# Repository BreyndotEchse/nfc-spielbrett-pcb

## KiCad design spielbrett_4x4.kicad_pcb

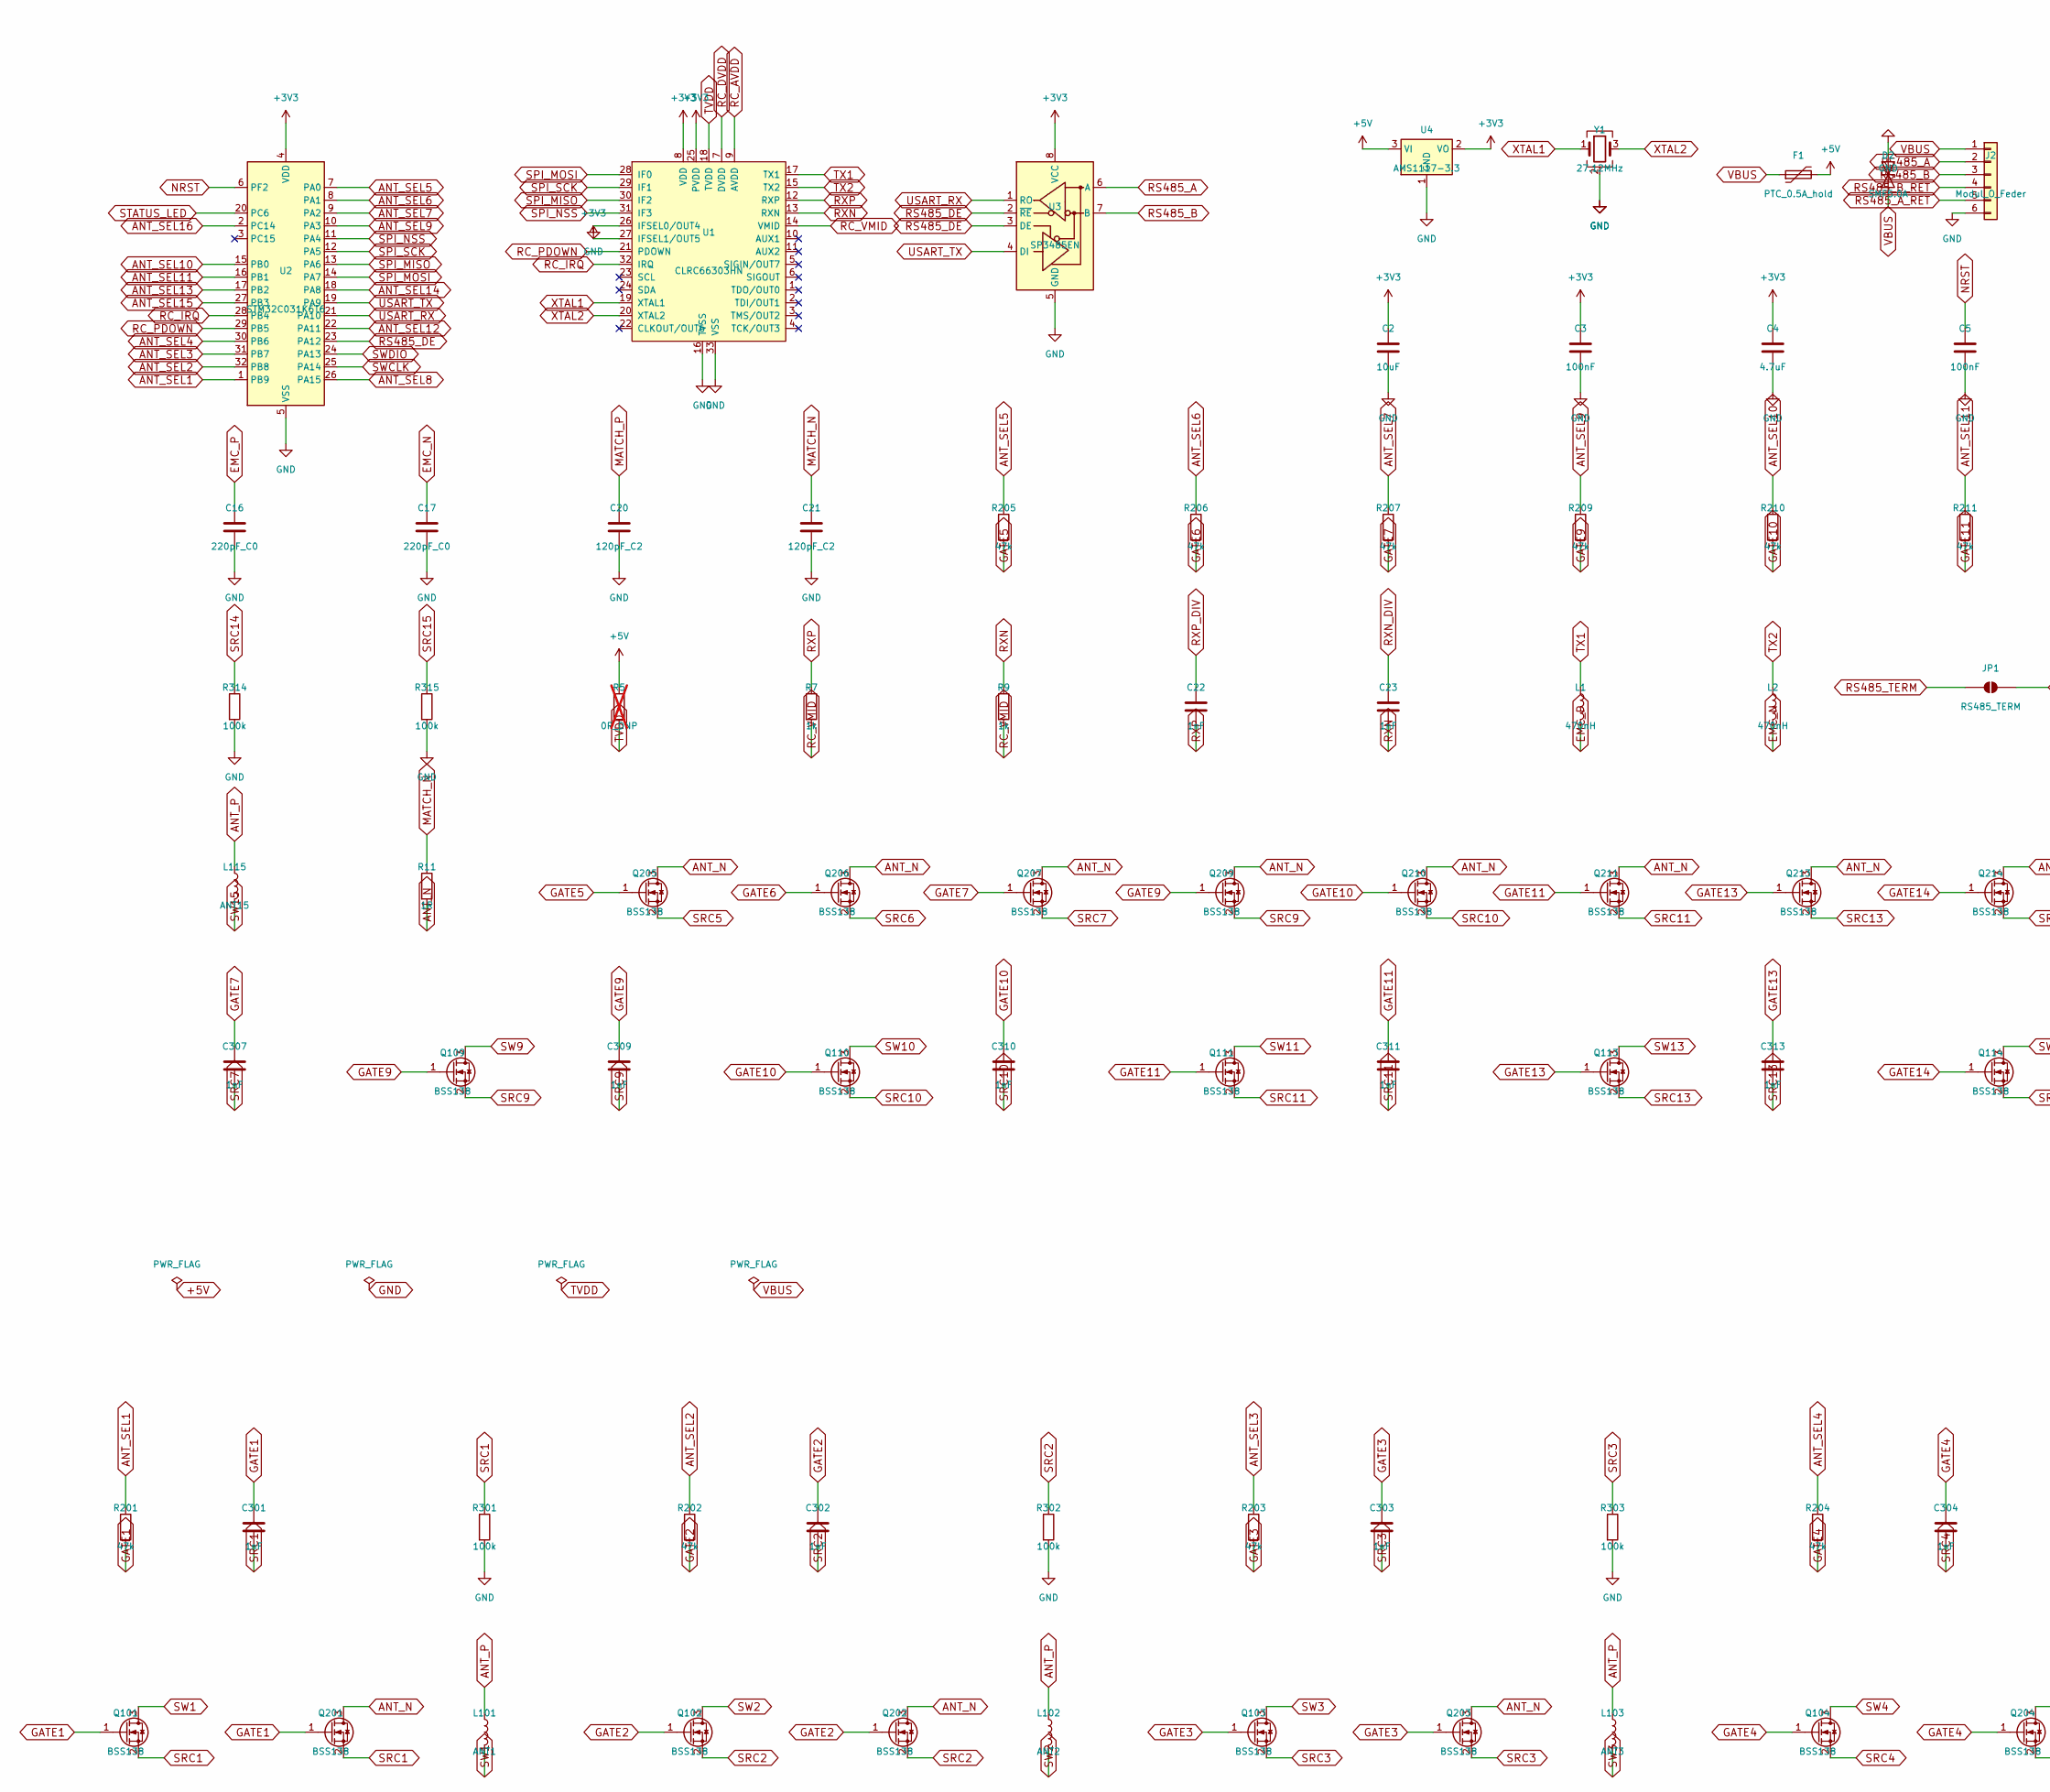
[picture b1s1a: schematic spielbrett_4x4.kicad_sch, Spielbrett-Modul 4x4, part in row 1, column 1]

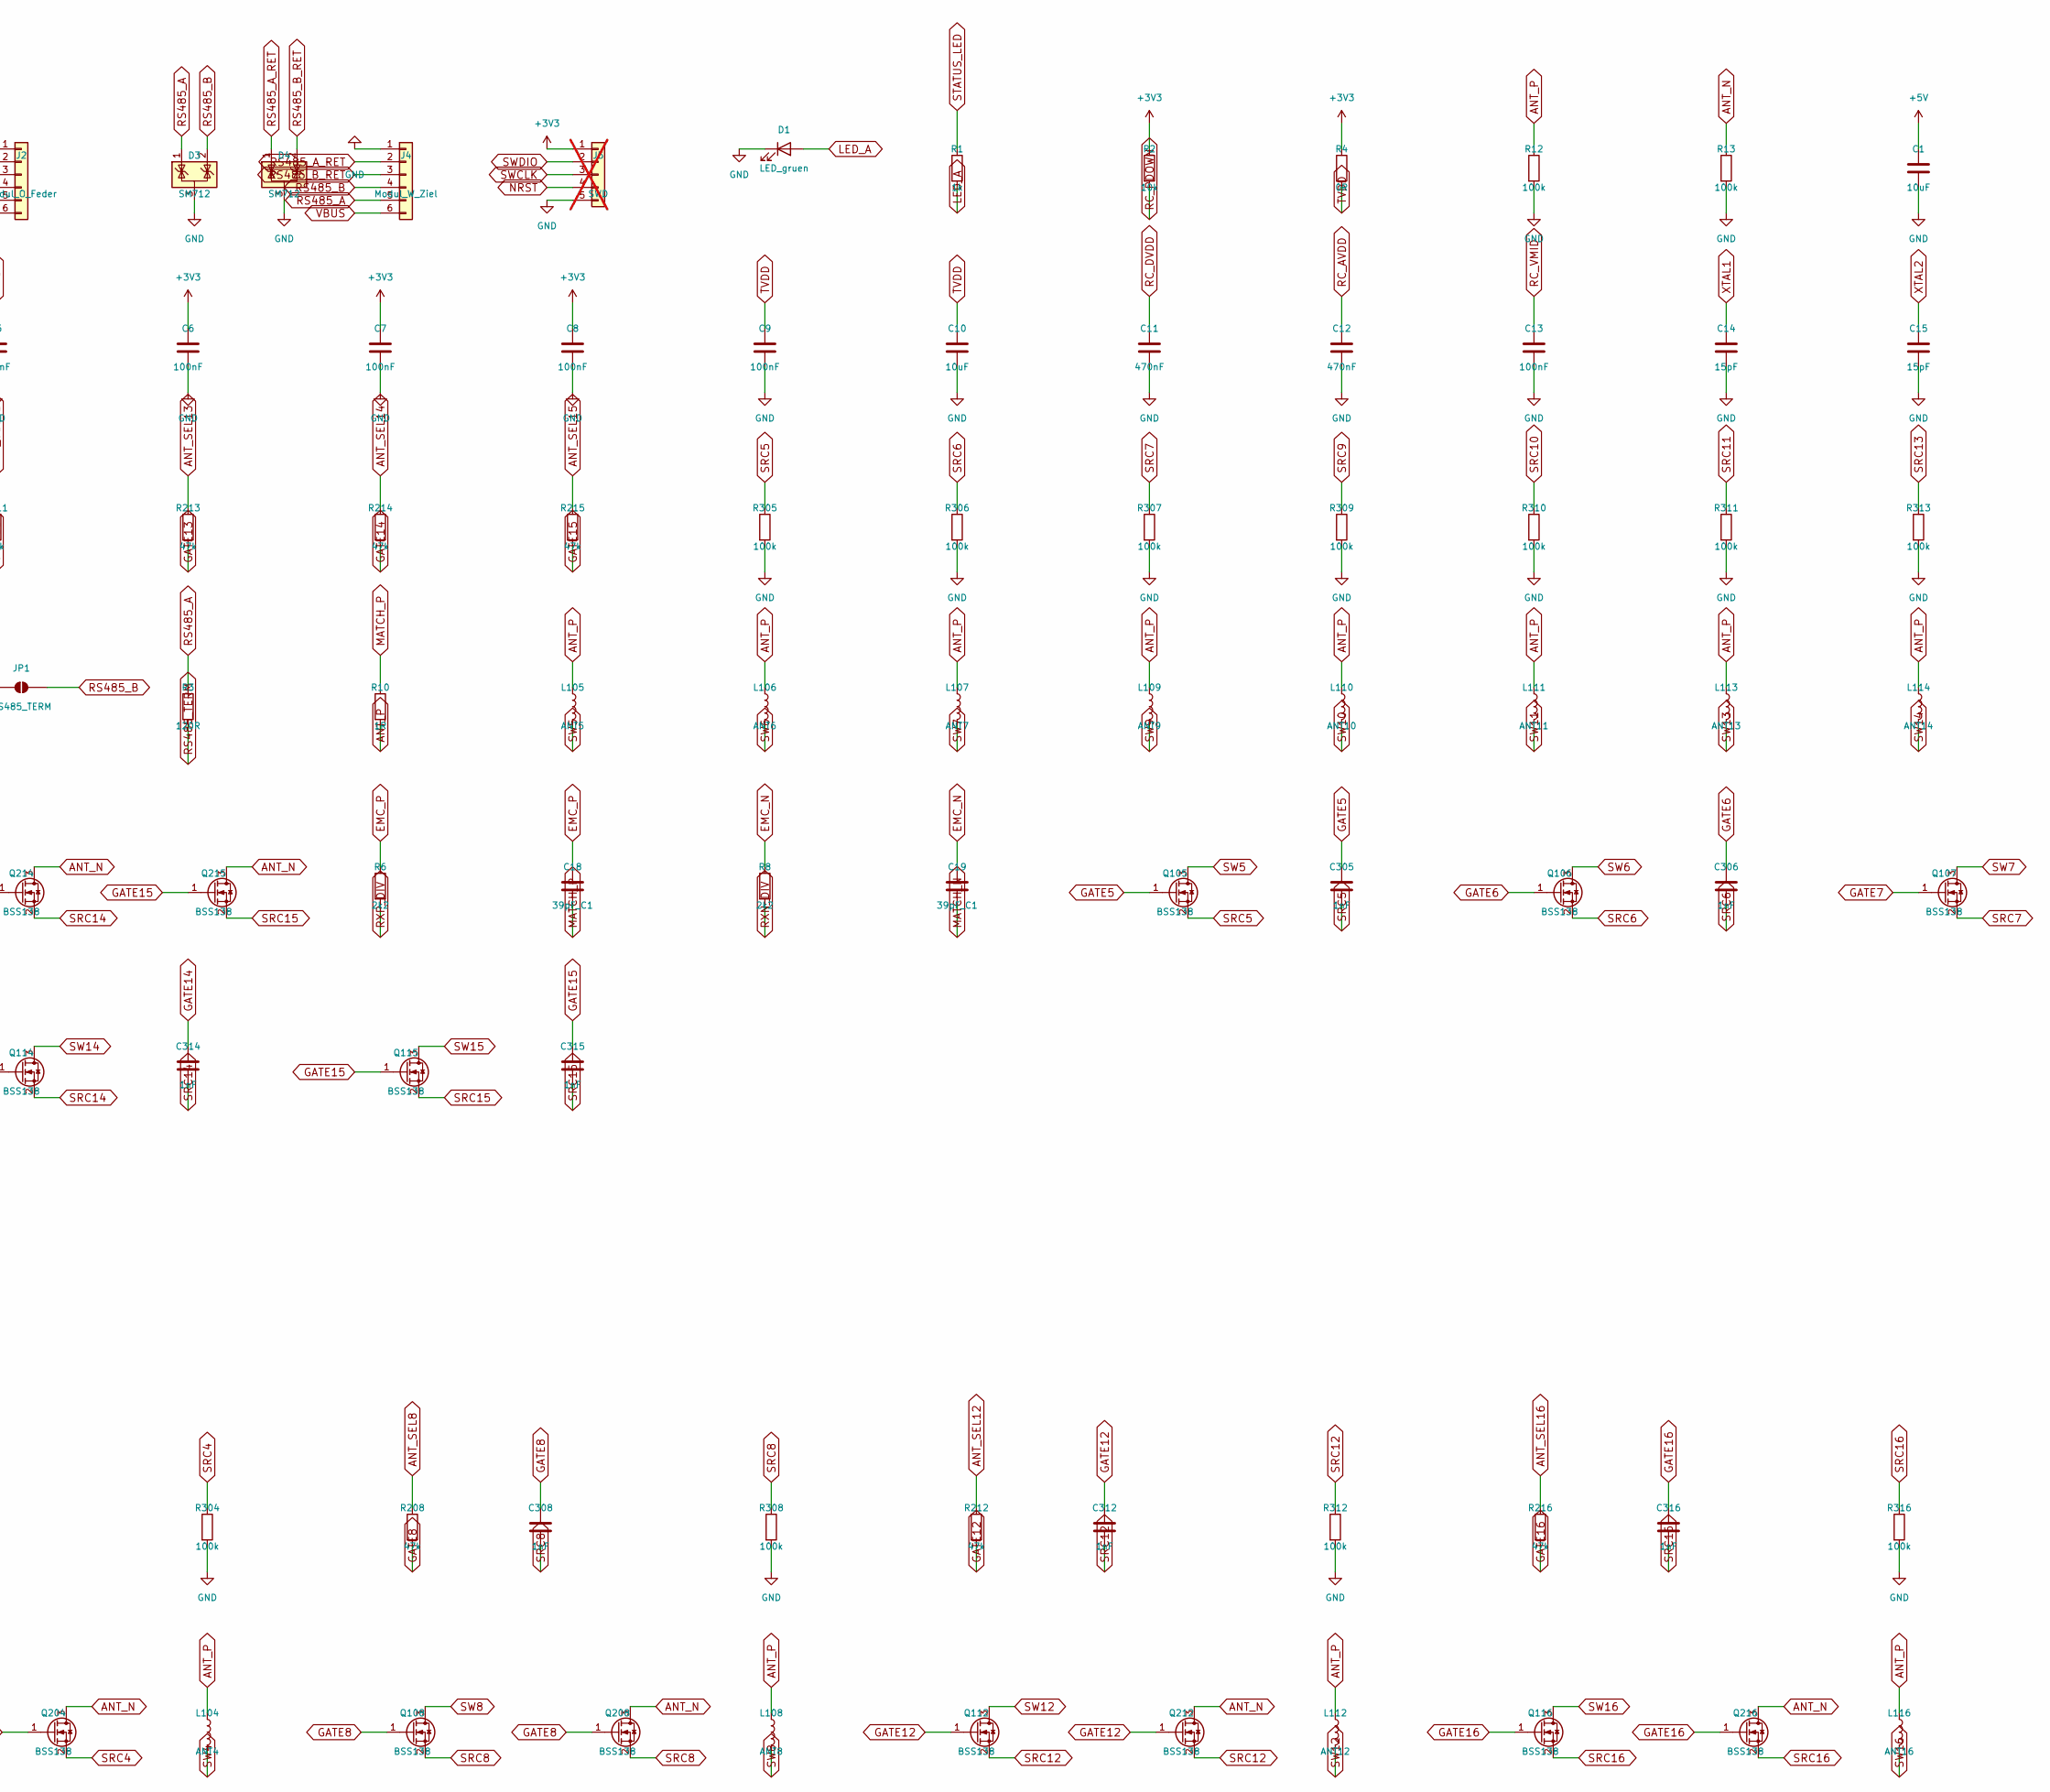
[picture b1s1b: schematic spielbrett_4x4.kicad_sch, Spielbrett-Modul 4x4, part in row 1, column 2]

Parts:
C1, C2, C10: 10uF; C_0805_2012Metric; LCSC C15850
C3, C5, C6, C7, C8, C9, C13: 100nF; C_0603_1608Metric; LCSC C14663
C4: 4.7uF; C_0603_1608Metric; LCSC C19666
C11, C12: 470nF; C_0603_1608Metric; LCSC C1623
C14, C15: 15pF; C_0603_1608Metric; LCSC C1644
C16, C17: 220pF_C0; C_0603_1608Metric; LCSC C106210
C18, C19: 39pF_C1; C_0603_1608Metric; LCSC C107049
C20, C21: 120pF_C2; C_0603_1608Metric; LCSC C107035
C22, C23, C301, C302, C303, C304, C305, C306, C307, C308, C309, C310, C311, C312, C313, C314, C315, C316: 1nF; C_0603_1608Metric; LCSC C1588
D1: LED_gruen; LED_0603_1608Metric; LCSC C12624
D2: SMF5.0A; D_SOD-123F; LCSC C19077497
D3, D4: SM712; SOT-23; LCSC C521963
F1: PTC_0.5A_hold; Fuse_1206_3216Metric; LCSC C7542947
J2: Modul_O_Feder; HC-CX-PH254-1x6PW-4050B-E; MPN HC-CX-PH254-1x6PW-4050B-E; LCSC C56314391
J4: Modul_W_Ziel; HC-CX-FH254-1x6PW-4040B-E; MPN HC-CX-FH254-1x6PW-4040B-E; LCSC C56314419
J5: SWD; PinHeader_1x05_P1.27mm_Vertical; not fitted
JP1: RS485_TERM; SolderJumper-2_P1.3mm_Open_RoundedPad1.0x1.5mm
L1, L2: 470nH; L_0805_2012Metric; LCSC C412002
L101: ANT1; NFC_Coil_D30_N4_W0.4_S0.4
L102: ANT2; NFC_Coil_D30_N4_W0.4_S0.4
L103: ANT3; NFC_Coil_D30_N4_W0.4_S0.4
L104: ANT4; NFC_Coil_D30_N4_W0.4_S0.4
L105: ANT5; NFC_Coil_D30_N4_W0.4_S0.4
L106: ANT6; NFC_Coil_D30_N4_W0.4_S0.4
L107: ANT7; NFC_Coil_D30_N4_W0.4_S0.4
L108: ANT8; NFC_Coil_D30_N4_W0.4_S0.4
L109: ANT9; NFC_Coil_D30_N4_W0.4_S0.4
L110: ANT10; NFC_Coil_D30_N4_W0.4_S0.4
L111: ANT11; NFC_Coil_D30_N4_W0.4_S0.4
L112: ANT12; NFC_Coil_D30_N4_W0.4_S0.4
L113: ANT13; NFC_Coil_D30_N4_W0.4_S0.4
L114: ANT14; NFC_Coil_D30_N4_W0.4_S0.4
L115: ANT15; NFC_Coil_D30_N4_W0.4_S0.4
L116: ANT16; NFC_Coil_D30_N4_W0.4_S0.4
Q101, Q102, Q103, Q104, Q105, Q106, Q107, Q108, Q109, Q110, Q111, Q112, Q113, Q114, Q115, Q116, Q201, Q202, Q203, Q204, Q205, Q206, Q207, Q208, Q209, Q210, Q211, Q212, Q213, Q214, Q215, Q216: BSS138; SOT-23; LCSC C7420339
R1, R7, R9: 1k; R_0603_1608Metric; LCSC C21190
R2: 10k; R_0603_1608Metric; LCSC C25804
R3: 120R; R_0603_1608Metric; LCSC C22787
R4: 0R; R_0805_2012Metric; LCSC C17477
R5: 0R_DNP; R_0805_2012Metric; LCSC C17477; not fitted
R6, R8: 2k2; R_0603_1608Metric; LCSC C4190
R10, R11: 1R; R_0603_1608Metric; LCSC C22936
R12, R13, R301, R302, R303, R304, R305, R306, R307, R308, R309, R310, R311, R312, R313, R314, R315, R316: 100k; R_0603_1608Metric; LCSC C25803
R201, R202, R203, R204, R205, R206, R207, R208, R209, R210, R211, R212, R213, R214, R215, R216: 47k; R_0603_1608Metric; LCSC C25819
U1: CLRC66303HN; HVQFN-32-1EP_5x5mm_P0.5mm_EP3.1x3.1mm; MPN CLRC66303HNY; LCSC C2988350
U2: STM32C031K6T6; LQFP-32_7x7mm_P0.8mm; MPN STM32C031K6T6; LCSC C5456169
U3: SP3485EN; SOIC-8_3.9x4.9mm_P1.27mm; MPN SP3485EN-L/TR; LCSC C8963
U4: AMS1117-3.3; SOT-223-3_TabPin2; LCSC C6186
Y1: 27.12MHz; Crystal_SMD_3225-4Pin_3.2x2.5mm; LCSC C29975

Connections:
+3V3: C2.1, C3.1, C4.1, C6.1, C7.1, C8.1, J5.1, R2.1, R4.1, U1.8 (VDD), U1.25 (PVDD), U1.27 (IFSEL1/OUT5), U2.4 (VDD), U3.8 (VCC), U4.2 (VO)
+5V: C1.1, F1.2, R5.1, U4.3 (VI)
ANT_N: Q201.3 (D), Q202.3 (D), Q203.3 (D), Q204.3 (D), Q205.3 (D), Q206.3 (D), Q207.3 (D), Q208.3 (D), Q209.3 (D), Q210.3 (D), Q211.3 (D), Q212.3 (D), Q213.3 (D), Q214.3 (D), Q215.3 (D), Q216.3 (D), R11.2, R13.1
ANT_P: L101.1, L102.1, L103.1, L104.1, L105.1, L106.1, L107.1, L108.1, L109.1, L110.1, L111.1, L112.1, L113.1, L114.1, L115.1, L116.1, R10.2, R12.1
ANT_SEL1: R201.1, U2.1 (PB9)
ANT_SEL2: R202.1, U2.32 (PB8)
ANT_SEL3: R203.1, U2.31 (PB7)
ANT_SEL4: R204.1, U2.30 (PB6)
ANT_SEL5: R205.1, U2.7 (PA0)
ANT_SEL6: R206.1, U2.8 (PA1)
ANT_SEL7: R207.1, U2.9 (PA2)
ANT_SEL8: R208.1, U2.26 (PA15)
ANT_SEL9: R209.1, U2.10 (PA3)
ANT_SEL10: R210.1, U2.15 (PB0)
ANT_SEL11: R211.1, U2.16 (PB1)
ANT_SEL12: R212.1, U2.22 (PA11)
ANT_SEL13: R213.1, U2.17 (PB2)
ANT_SEL14: R214.1, U2.18 (PA8)
ANT_SEL15: R215.1, U2.27 (PB3)
ANT_SEL16: R216.1, U2.2 (PC14)
EMC_N: C17.1, C19.1, L2.2, R8.1
EMC_P: C16.1, C18.1, L1.2, R6.1
GATE1: C301.1, Q101.1 (G), Q201.1 (G), R201.2
GATE2: C302.1, Q102.1 (G), Q202.1 (G), R202.2
GATE3: C303.1, Q103.1 (G), Q203.1 (G), R203.2
GATE4: C304.1, Q104.1 (G), Q204.1 (G), R204.2
GATE5: C305.1, Q105.1 (G), Q205.1 (G), R205.2
GATE6: C306.1, Q106.1 (G), Q206.1 (G), R206.2
GATE7: C307.1, Q107.1 (G), Q207.1 (G), R207.2
GATE8: C308.1, Q108.1 (G), Q208.1 (G), R208.2
GATE9: C309.1, Q109.1 (G), Q209.1 (G), R209.2
GATE10: C310.1, Q110.1 (G), Q210.1 (G), R210.2
GATE11: C311.1, Q111.1 (G), Q211.1 (G), R211.2
GATE12: C312.1, Q112.1 (G), Q212.1 (G), R212.2
GATE13: C313.1, Q113.1 (G), Q213.1 (G), R213.2
GATE14: C314.1, Q114.1 (G), Q214.1 (G), R214.2
GATE15: C315.1, Q115.1 (G), Q215.1 (G), R215.2
GATE16: C316.1, Q116.1 (G), Q216.1 (G), R216.2
GND: C1.2, C2.2, C3.2, C4.2, C5.2, C6.2, C7.2, C8.2, C9.2, C10.2, C11.2, C12.2, C13.2, C14.2, C15.2, C16.2, C17.2, C20.2, C21.2, D1.1 (K), D2.2 (A2), D3.3 (A), D4.3 (A), J2.6, J4.1, J5.5, R12.2, R13.2, R301.2, R302.2, R303.2, R304.2, R305.2, R306.2, R307.2, R308.2, R309.2, R310.2, R311.2, R312.2, R313.2, R314.2, R315.2, R316.2, U1.16 (TVSS), U1.26 (IFSEL0/OUT4), U1.33 (VSS), U2.5 (VSS), U3.5 (GND), U4.1 (GND), Y1.2 (G), Y1.4 (G)
LED_A: D1.2 (A), R1.2
MATCH_N: C19.2, C21.1, R11.1
MATCH_P: C18.2, C20.1, R10.1
NRST: C5.1, J5.4, U2.6 (PF2)
RC_AVDD: C12.1, U1.9 (AVDD)
RC_DVDD: C11.1, U1.7 (DVDD)
RC_IRQ: U1.32 (IRQ), U2.28 (PB4)
RC_PDOWN: R2.2, U1.21 (PDOWN), U2.29 (PB5)
RC_VMID: C13.1, R7.2, R9.2, U1.14 (VMID)
RS485_A: D3.1 (K), J2.2, J4.5, R3.1, U3.6 (A)
RS485_A_RET: D4.1 (K), J2.5, J4.2
RS485_B: D3.2 (K), J2.3, J4.4, JP1.2 (B), U3.7 (B)
RS485_B_RET: D4.2 (K), J2.4, J4.3
RS485_DE: U2.23 (PA12), U3.2 (~RE), U3.3 (DE)
RS485_TERM: JP1.1 (A), R3.2
RXN: C23.2, R9.1, U1.13 (RXN)
RXN_DIV: C23.1, R8.2
RXP: C22.2, R7.1, U1.12 (RXP)
RXP_DIV: C22.1, R6.2
SPI_MISO: U1.30 (IF2), U2.13 (PA6)
SPI_MOSI: U1.28 (IF0), U2.14 (PA7)
SPI_NSS: U1.31 (IF3), U2.11 (PA4)
SPI_SCK: U1.29 (IF1), U2.12 (PA5)
SRC1: C301.2, Q101.2 (S), Q201.2 (S), R301.1
SRC2: C302.2, Q102.2 (S), Q202.2 (S), R302.1
SRC3: C303.2, Q103.2 (S), Q203.2 (S), R303.1
SRC4: C304.2, Q104.2 (S), Q204.2 (S), R304.1
SRC5: C305.2, Q105.2 (S), Q205.2 (S), R305.1
SRC6: C306.2, Q106.2 (S), Q206.2 (S), R306.1
SRC7: C307.2, Q107.2 (S), Q207.2 (S), R307.1
SRC8: C308.2, Q108.2 (S), Q208.2 (S), R308.1
SRC9: C309.2, Q109.2 (S), Q209.2 (S), R309.1
SRC10: C310.2, Q110.2 (S), Q210.2 (S), R310.1
SRC11: C311.2, Q111.2 (S), Q211.2 (S), R311.1
SRC12: C312.2, Q112.2 (S), Q212.2 (S), R312.1
SRC13: C313.2, Q113.2 (S), Q213.2 (S), R313.1
SRC14: C314.2, Q114.2 (S), Q214.2 (S), R314.1
SRC15: C315.2, Q115.2 (S), Q215.2 (S), R315.1
SRC16: C316.2, Q116.2 (S), Q216.2 (S), R316.1
STATUS_LED: R1.1, U2.20 (PC6)
SW1: L101.2, Q101.3 (D)
SW2: L102.2, Q102.3 (D)
SW3: L103.2, Q103.3 (D)
SW4: L104.2, Q104.3 (D)
SW5: L105.2, Q105.3 (D)
SW6: L106.2, Q106.3 (D)
SW7: L107.2, Q107.3 (D)
SW8: L108.2, Q108.3 (D)
SW9: L109.2, Q109.3 (D)
SW10: L110.2, Q110.3 (D)
SW11: L111.2, Q111.3 (D)
SW12: L112.2, Q112.3 (D)
SW13: L113.2, Q113.3 (D)
SW14: L114.2, Q114.3 (D)
SW15: L115.2, Q115.3 (D)
SW16: L116.2, Q116.3 (D)
SWCLK: J5.3, U2.25 (PA14)
SWDIO: J5.2, U2.24 (PA13)
TX1: L1.1, U1.17 (TX1)
TX2: L2.1, U1.15 (TX2)
USART_RX: U2.21 (PA10), U3.1 (RO)
USART_TX: U2.19 (PA9), U3.4 (DI)
XTAL1: C14.1, U1.19 (XTAL1), Y1.1
XTAL2: C15.1, U1.20 (XTAL2), Y1.3

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
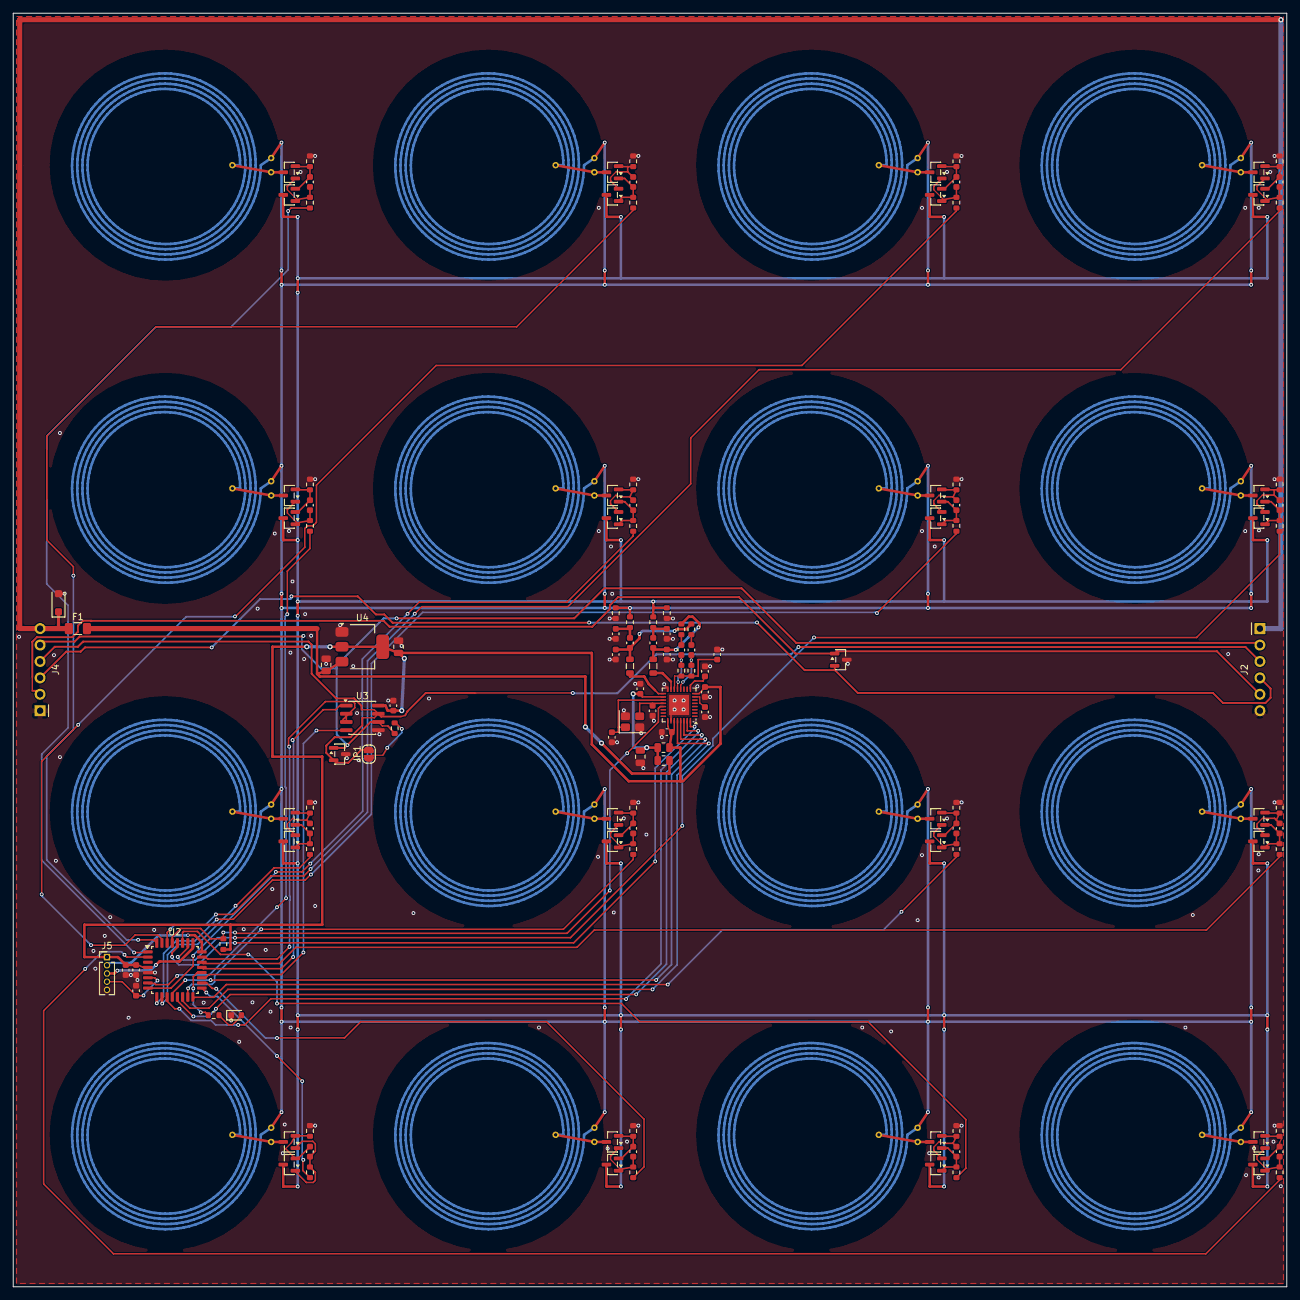
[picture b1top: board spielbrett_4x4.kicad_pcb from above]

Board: 2 copper layers, 197.0 x 197.0 mm, 148 parts (0 on the bottom side), 105 nets.

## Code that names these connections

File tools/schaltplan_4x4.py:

"""Schaltplan des 4x4-Moduls (spielbrett_4x4.kicad_sch) aus dem 3x3-Schaltplan erzeugen.

  python tools/schaltplan_4x4.py

Das 4x4-Brett entsteht aus dem 3x3-Brett, indem rechts eine Spalte und oben eine Reihe Felder
angesetzt werden. Die Spulen werden im 4x4-Raster zeilenweise neu nummeriert (ANT1 oben links,
ANT16 unten rechts); die bisherigen 9 Spulen liegen in den Reihen 2-4 / Spalten 1-3.

  * Referenzen je Spule k (1..16): L1kk Spule, Q1kk Schalter Spulenseite, Q2kk Schalter ANT_N,
    R2kk Gate-Widerstand, R3kk Source-Bezug, C3kk Gate-Kondensator (z. B. L101, Q216)
  * Netze je Spule: ANT_SELk, GATEk, SRCk, SWk; Spulenwert ANTk
  * Die 7 neuen Spulengruppen sind Kopien der bisherigen Gruppe 9 (unten auf dem Blatt)
  * Neue Auswahlleitungen an bisher freien MCU-Pins (PC15 bleibt frei):
      ANT_SEL1 PB9, ANT_SEL2 PB8, ANT_SEL3 PB7, ANT_SEL4 PB6 (obere Reihe),
      ANT_SEL8 PA15, ANT_SEL12 PA11, ANT_SEL16 PC14 (rechte Spalte)
"""
import re
import uuid
from pathlib import Path

PRJ = Path(__file__).resolve().parent.parent
SRC = PRJ / "spielbrett.kicad_sch"
DST = PRJ / "spielbrett_4x4.kicad_sch"

OLD_N, NEW_N = 3, 4


def new_k(k_old):
    r, c = divmod(k_old - 1, OLD_N)
    return (r + 1) * NEW_N + c + 1


MAP = {k: new_k(k) for k in range(1, OLD_N * OLD_N + 1)}           # 1->5 ... 9->15
NEW_COILS = sorted(set(range(1, NEW_N * NEW_N + 1)) - set(MAP.values()))
# MCU-Pin (Pin-Endpunkt im Schaltplan) je neuer Auswahlleitung; Seite L = links (Label nach links)
GPIO = {1: ("L", 102.87), 2: ("L", 100.33), 3: ("L", 97.79), 4: ("L", 95.25),
        8: ("R", 102.87), 12: ("R", 92.71), 16: ("L", 72.39)}
PIN_X = {"L": 62.23, "R": 82.55}


def refs(k):
    return {"L": f"L{100 + k}", "Q": f"Q{100 + k}", "QN": f"Q{200 + k}",
            "RG": f"R{200 + k}", "RS": f"R{300 + k}", "C": f"C{300 + k}"}


def old_refs(k):
    return {"L": f"L1{k}", "Q": f"Q{k}", "QN": f"Q1{k}", "RG": f"R2{k}", "RS": f"R3{k}", "C": f"C3{k}"}


def blocks(s):
    """Top-Level-Elemente (Einrueckung ein Tab) als (start, ende)."""
    out = []
    for m in re.finditer(r"^\t\(", s, re.M):
        a = m.start()
        b = s.find("\n\t)\n", a)
        nl = s.find("\n", a)
        if s[a:nl].rstrip().endswith(")"):        # einzeiliges Element
            b = nl
        else:
            b += 3
        out.append((a, b))
    return out


def pts(blk):
    p = re.findall(r"\(xy ([\d.\-]+) ([\d.\-]+)\)", blk) if blk.startswith("\t(wire") else []
    if not p:
        m = re.search(r"\(at ([\d.\-]+) ([\d.\-]+)", blk)
        p = [m.groups()] if m else []
    return [(float(x), float(y)) for x, y in p]


def fmt(v):
    r = round(v, 4)
    return str(int(r)) if r == int(r) else repr(r)


def shift(blk, dx, dy):
    def f(m):
        return f"({m.group(1)} {fmt(float(m.group(2)) + dx)} {fmt(float(m.group(3)) + dy)}"
    return re.sub(r"\((at|xy) ([\d.\-]+) ([\d.\-]+)", f, blk)


def fresh_uuids(blk):
    return re.sub(r'\(uuid "[0-9a-f-]{36}"\)', lambda m: f'(uuid "{uuid.uuid4()}")', blk)


def main():
    s = SRC.read_text(encoding="utf-8").replace("\r\n", "\n")

    # 1) bestehende 9 Spulengruppen umbenennen (gleichzeitig, ohne Verkettung)
    ref_map = {}
    for k_old, k in MAP.items():
        for key, old in old_refs(k_old).items():
            ref_map[old] = refs(k)[key]
    s = re.sub(r'(\(property "Reference" |\(reference )"([^"]+)"',
               lambda m: f'{m.group(1)}"{ref_map.get(m.group(2), m.group(2))}"', s)
    s = re.sub(r'\(global_label "(ANT_SEL|GATE|SRC|SW)(\d+)"',
               lambda m: f'(global_label "{m.group(1)}{MAP[int(m.group(2))]}"', s)
    s = re.sub(r'\(property "Value" "ANT(\d)"', lambda m: f'(property "Value" "ANT{MAP[int(m.group(1))]}"', s)
    s = s.replace('(project "spielbrett"', '(project "spielbrett_4x4"')
    s = re.sub(r'\(title "[^"]*"\)', '(title "Spielbrett-Modul 4x4")', s, count=1)

    # 2) Vorlage: Gruppe der bisherigen Spule 9 (jetzt 15) -- je Bauteil Symbol + Draehte + Labels
    bl = blocks(s)
    tpl_k = MAP[9]
    tpl = {}
    for key, ref in refs(tpl_k).items():
        sym = next((a, b) for a, b in bl if s[a:b].startswith("\t(symbol")
                   and f'(property "Reference" "{ref}"' in s[a:b])
        c = pts(s[sym[0]:sym[1]])[0]
        members = [s[a:b] for a, b in bl
                   if not s[a:b].startswith("\t(lib_symbols")
                   and any(abs(x - c[0]) < 13 and abs(y - c[1]) < 13 for x, y in pts(s[a:b]))]
        tpl[key] = (c, members)

    pwr = max(int(n) for n in re.findall(r'"#PWR(\d+)"', s))
    G = 1.27
    slots = {"RG": (0, 260), "C": (20, 260), "RS": (56, 260), "Q": (0, 292), "QN": (32, 292), "L": (56, 292)}
    add = []
    for j, k in enumerate(NEW_COILS):
        bx = 32 + 88 * j                                          # Rastereinheiten (1,27 mm)
        for key, (c, members) in tpl.items():
            sx, sy = slots[key]
            dx, dy = (bx + sx) * G - c[0], sy * G - c[1]
            for blk in members:
                b = shift(fresh_uuids(blk), dx, dy)
                for kk, ref in refs(tpl_k).items():
                    b = b.replace(f'"{ref}"', f'"{refs(k)[kk]}"')
                b = re.sub(r'"(ANT_SEL|GATE|SRC|SW)%d"' % tpl_k, lambda m: f'"{m.group(1)}{k}"', b)
                b = b.replace(f'"ANT{tpl_k}"', f'"ANT{k}"')
                if '"#PWR' in b:
                    pwr += 1
                    b = re.sub(r'"#PWR\d+"', f'"#PWR{pwr:03d}"', b)
                add.append(b)

    # 3) MCU: freie Pins (No-Connect) durch Draht + Label ANT_SELk ersetzen
    lab = {}
    for side, name in (("L", "ANT_SEL15"), ("R", "ANT_SEL14")):   # vorhandene Labels als Vorlage
        m = re.search(r'\t\(global_label "%s"\n\t\t\(shape bidirectional\)\n\t\t\(at (%s) ([\d.]+)' %
                      (name, "55.88" if side == "L" else "88.9"), s)
        a = m.start()
        lab[side] = (s[a:s.find("\n\t)\n", a) + 3], float(m.group(2)))
    for k, (side, y) in GPIO.items():
        px = PIN_X[side]
        nc = re.search(r'\t\(no_connect\n\t\t\(at %s %s\)\n.*?\n\t\)\n' % (re.escape(f"{px:g}"), re.escape(f"{y:g}")), s)
        if not nc:
            raise SystemExit(f"Kein No-Connect an MCU-Pin {side} y={y}")
        s = s[:nc.start()] + s[nc.end():]
        lx = px - 6.35 if side == "L" else px + 6.35
        add.append(f'\t(wire\n\t\t(pts (xy {px:g} {y:g}) (xy {lx:g} {y:g}))\n'
                   f'\t\t(stroke (width 0) (type solid))\n\t\t(uuid "{uuid.uuid4()}")\n\t)\n')
        blk, y0 = lab[side]
        b = shift(fresh_uuids(blk), 0, y - y0)
        b = re.sub(r'\(global_label "ANT_SEL\d+"', f'(global_label "ANT_SEL{k}"', b)
        add.append(b)

    i = s.index("\t(sheet_instances")
    s = s[:i] + "".join(a if a.endswith("\n") else a + "\n" for a in add) + s[i:]
    DST.write_bytes(s.replace("\n", "\r\n").encode("utf-8"))
    print(f"{DST.name}: {len(NEW_COILS)} neue Spulengruppen ({NEW_COILS}), Umbenennung {MAP}")


if __name__ == "__main__":
    main()

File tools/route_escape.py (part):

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
Alles landet gesperrt in der Gruppe "Escape_Routing"; ein erneuter Lauf ersetzt nur diese Gruppe.

RX     RXN (Pin 13) / RXP (Pin 12) per Via unter den VMID-Pads von R9/R7 hindurch auf B.Cu zum
       Knoten R.1/C.2 (eine Kreuzung VMID <-> RX ist bei dieser Pinfolge topologisch unvermeidbar).
VMID   Pin 14 -> R9.2 -> R7.2 -> rechts hoch -> C13.
AVDD   Pin 9 -> C12.1, DVDD Pin 7 -> C11.1.
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    t([p14, (xv, 84.0), (xv, r9v[1]), r9v], "RC_VMID", w=FINE)
    t([r9v, r7v, (xr, r7v[1]), (xr, c13v[1]), c13v], "RC_VMID", w=SIG)

    # ---------- RXN: Pin 13 -> Via -> B.Cu -> Via zwischen C23.2 und R9.1 ----------
    p13, r9n, c23n = P("U1", 13), P("R9", 1), P("C23", 2)
    vn = (p13[0] + 0.1, 83.45)
    vn2 = (r9n[0], (r9n[1] + c23n[1]) / 2)
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    r.via(vn2, "RXN", SMALL_VIA)
    t([r9n, vn2, c23n], "RXN", w=SIG)

    # ---------- RXP: Pin 12 -> Via -> B.Cu -> Via zwischen C22.2 und R7.1 ----------
    p12, r7p, c22p = P("U1", 12), P("R7", 1), P("C22", 2)
    vp = (p12[0] + 0.35, 83.45)
    vp2 = (r7p[0], (r7p[1] + c22p[1]) / 2)
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    t([p26, (p26[0], ep[1] + 1.2)], "GND", w=SIG)

    # ---------- SPI/IRQ: gestaffelte Ausfaecherung nach rechts unten ----------
    for i, (pin, net) in enumerate([(32, "RC_IRQ"), (31, "SPI_NSS"), (30, "SPI_MISO"),
                                    (29, "SPI_SCK"), (28, "SPI_MOSI")]):
        p = P("U1", pin)
        y = 90.35 + 0.65 * i
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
